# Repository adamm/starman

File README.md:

# Starman Christmas Tree Topper

Disclaimer: This work is a *work-in-progress*.  While this project is still
under active development, version 2.1 was released _December 1st, 2022_.
What you see here is code that is largely incomplete, buggy, crashes,
and could catch fire. The PCB board is largely inefficient, expensive,
broken, and could catch fire.

Version 1 of the star is a POC I created a few years ago which was literally
a 3d-printed star with 24 LEDs hot-glued onto it, driven by a LED PWM
module from Adafruit, 3 PWM channels for audio, running from an Arduino Uno.

Version 2 is a complete redesign for 2022, including a custom PCB, 144
LEDs, 235 components, ESP32-S3 MCU, esp-idf framework, and WiFi/Bluetooth
support.  Audio is driven by 4 PWM channels, featuring a volume control and
a class-D amplifier.

Version 2.1 includes over-the-air firmware updates. I plan on releasing
new themes and songs every Holiday season. 

As of December 2023, there are **7 themes** and **81 arranged songs**.

> [!NOTE]
> I'll be demoing the Starman project, as well demoing its build process at [Calgary Maker Faire, May 4 & 5 2024](https://calgary.makerfaire.com/).
> Come talk to me if you are interested in purchasing a pre-built Starman for Christmas 2024!

You can see v2 in action here: https://www.youtube.com/watch?v=h6fquYPDars

The PCB is created using KiCad:

The sound module connects to the spine of the star through 20mm pin socket
risers.  Finally, a 3d-printed mount secures the display to the christmas
tree's top branch via the risers:

I plan on producing 10 units for friends and family for Christmas 2022.
Right now the costs are too high to mass produce, so perhaps sometime in
2023 I can simplify the design and cut costs for general orders.

## HOW TO PLAY

- Press the button to start the game.
- Start the game with three lives at level 1 (overworld).  If you lose all lives, it's game over.
- There is a 50% chance you will complete each level.  If you do, you move onto next level.  If not, you die and need to retry.
  - Death can occur randomly within the level.
  - Press the button again to start the next level, or retry the same level.
- There is a 40% chance you'll get a star.
  - Stars can occur randomly within the level.
  - Stars do not negate death (ie, falling into a pit).
- There is a 25% chance you'll get a 1-up, resulting in an extra life.
- If you make it to level 4 (castle) and complete it, there is a 25% chance the princess will be there and the game is over.

## Installation

1. Install Starman at the top of your tree, or on your desk, shelf, or wall.
2. Connect the play button remote cable to the play button port.  Hide the play button in your tree, desk, shelf, or wall.
3. Power it on.
4. (Optiona) Connect to your wifi network (see below) to configure the brightness and theme.
5. Press the physical play button, or press Play on the Starman web app

### Wifi Setup

1. Power on the Starman
2. Watch for a "starman_######" access point, and connect to it.
3. Search for your home Wifi, and enter the credentials
  - Starman can only connect to 2.4Ghz/WPA2 endpoints
4. Once connected, wait for your IP address to scroll past the screen
5. Open the IP address in your web browser
  - You can now use this site to play Starman directly, and to access the internal API.

If you ever want to factory reset Starman, follow this procedure:
1. Press and hold *Play* button
2. Press and release *Reset* button
3. Release *Play* button
Starman will forget about its current wifi configuration, theme, and configuration. Follow the Wifi Setup instructions above to set it back up again.

## TODO

- [X] Finalize PCB design
- [X] Play music
- [X] Implement game logic
- [X] Unique light pattern per music song/state
- [X] Flash lights in sequence with music
- [X] GPIO play button
- [X] Show simple text messages
- [X] WiFi onboarding process
- [X] Over-the-air firmware updates
- [X] WiFi play button
- [X] HTTP REST API to push text, play sound
- [X] Brightness control
- [X] Selectable themes
- [ ] Document the REST API
- [ ] Upgrade the speaker from 800mW to 1.5W for more power
- [ ] Debug the RC filter to reduce distortion

## Known Issues

- v2.1 PCB has a label that says it supports 7 to 12 volts power.  *WARNING: only 6-7V is actually supported in v2.1 hardware. __Do not connect more than 7 volts!__*
- Only 2.4Gz WPA2 wifi is supported   (Cannot connect to 5Gz or WPA Enterprise)
- Sound gets distorted at high volume levels.
- It can take a long time after startup to get an IP address and start
  the web service
- Even though wifi and the web service are online and functioning, the
  index.html sometimes takes a long time to load
- Sometimes the device spontaneously resets if wifi connection is not
  stable or strong enough
- Some songs are way too long. (>60s)
- Some songs end way too early (<3s) with a "course completed" event.

## Milestones

2022-09-01
- PCB layout identified and key components selected

2022-09-25
- Components ordered and footprints verified

2022-09-27
- Upgrade from ESP32-S2 to ESP32-S3

2022-09-29
- PCB design delivered for production

2022-10-09
- Complete migration of core game logic from Arduino version (v1) to esp-idf version (v2)

2022-10-29
- Framework for connecting to wifi / performing OTA updates

2022-11-02
- Framework for showing basic text messages, like "Game Over", "Connect to Wifi", "Firmware Update in progress", etc

2022-11-27
- Manufacturing is complete for 10 units for friends and family.

## Key Components

- ESP32-S3-Mini module

- 9x LED1642GW drivers

- 144 OSRAM LY P47 2mm LEDs

- PAM8302A amplifer

- 239 total components (35 unique)

- Translate MIDI to Playtune C array
  - https://github.com/lenshustek/miditones

## Build Dependencies

- See [BUILDING](BUILDING.md) document.

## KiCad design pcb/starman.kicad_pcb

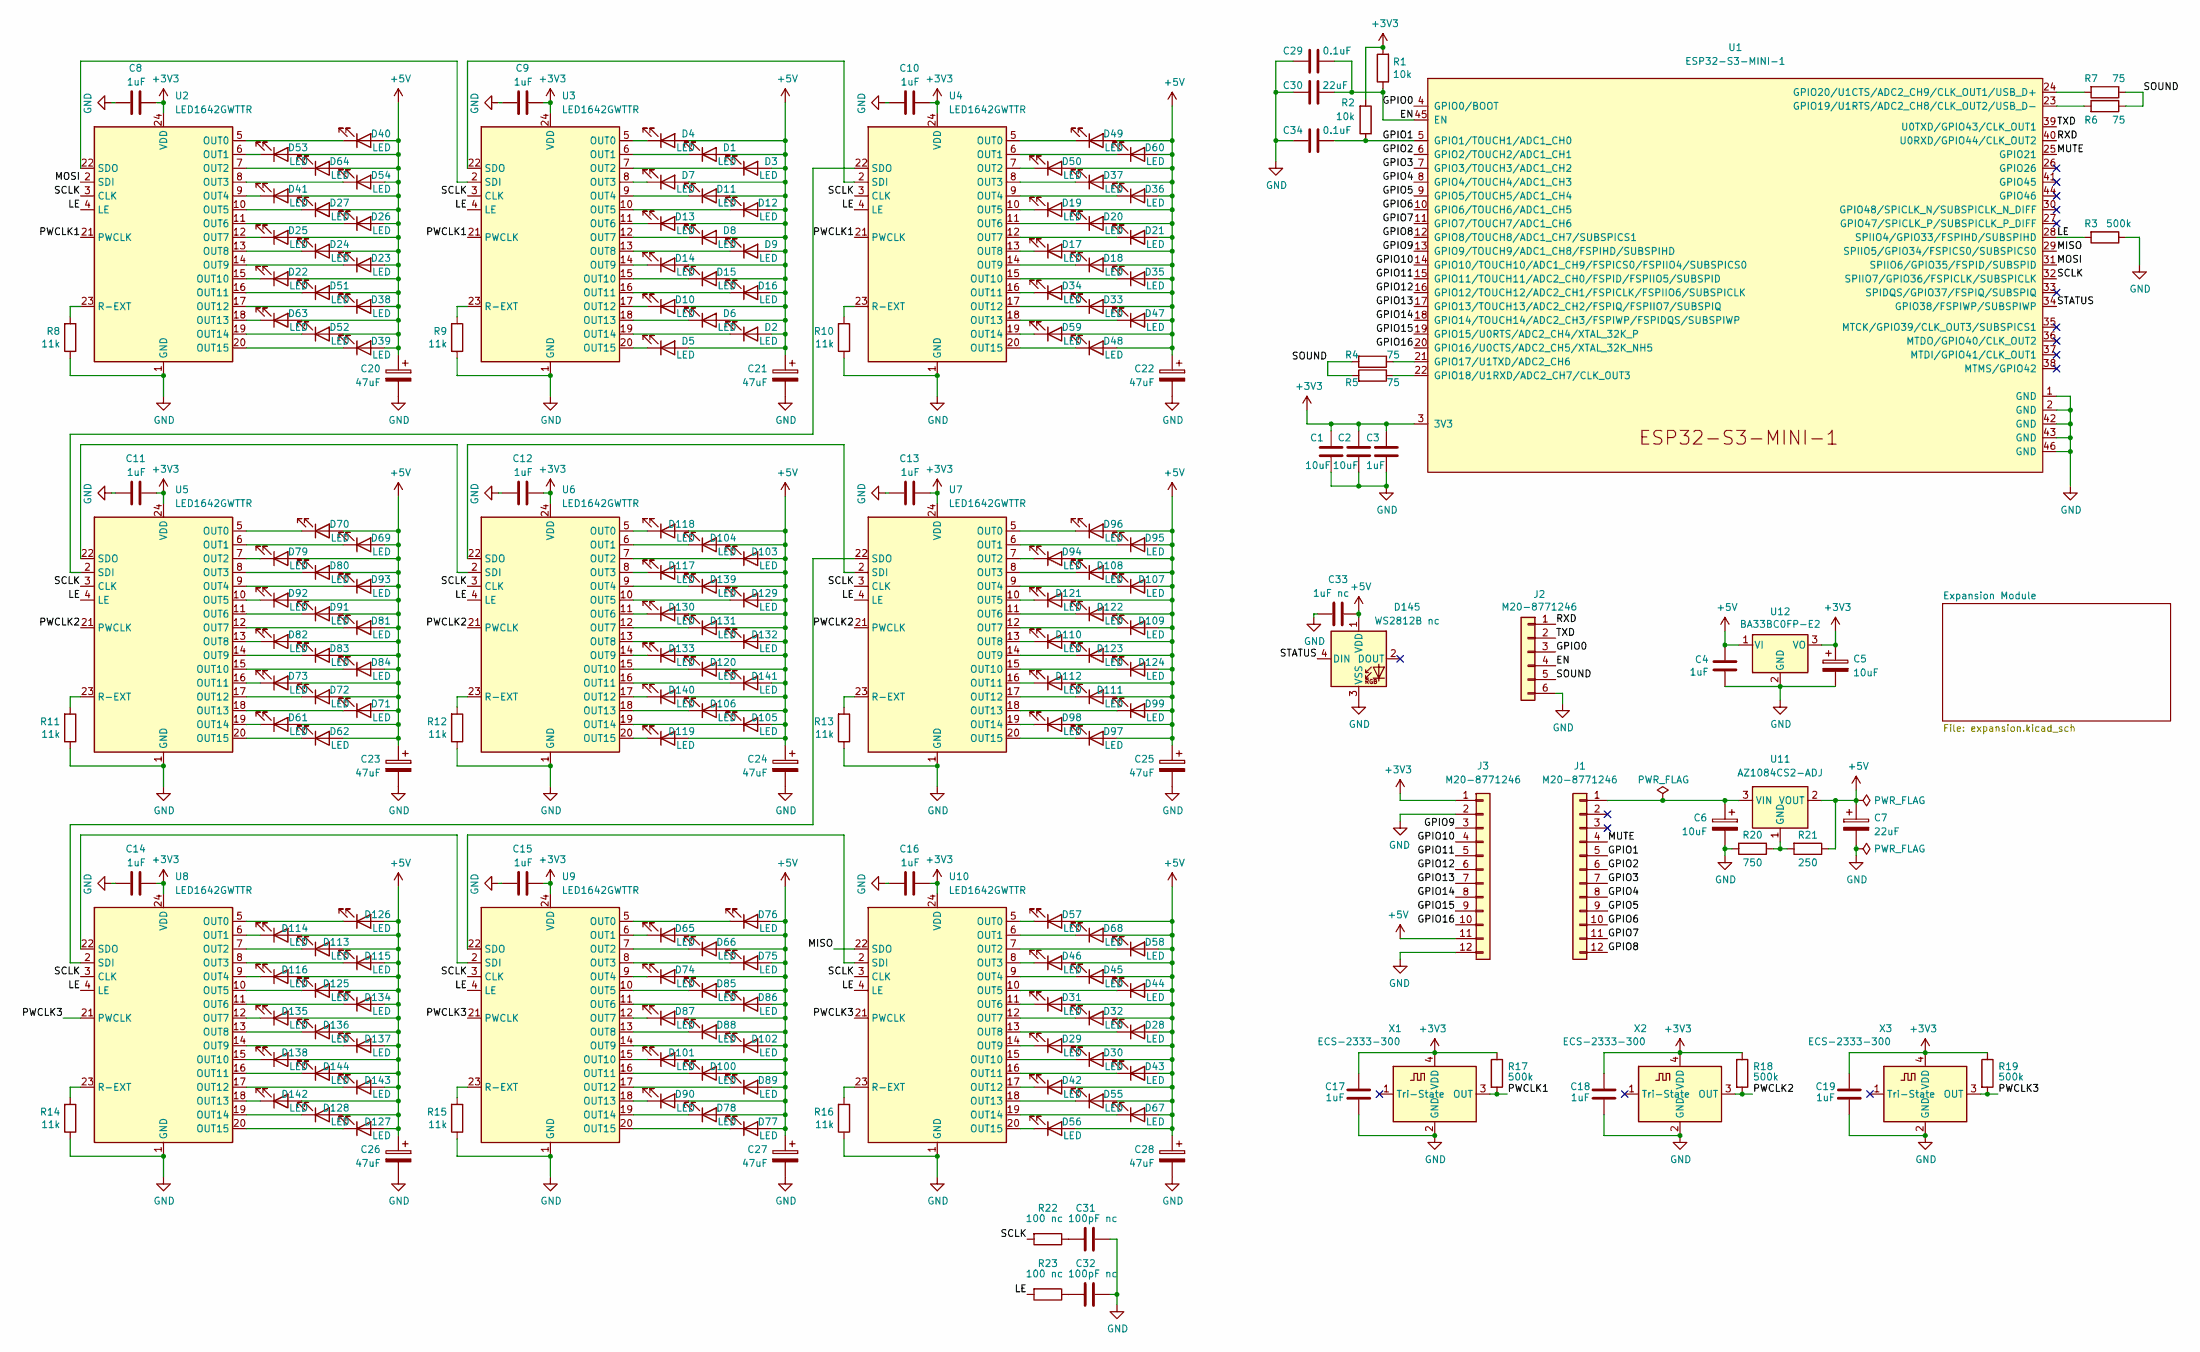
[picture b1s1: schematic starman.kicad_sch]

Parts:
C1, C2: 10uF; C_0805_2012Metric
C3, C4, C8, C9, C10, C11, C12, C13, C14, C15, C16, C17, C18, C19: 1uF; C_0805_2012Metric
C5, C6: 10uF; CP_EIA-3216-10_Kemet-I
C7: 22uF; CP_EIA-3216-10_Kemet-I
C20, C21, C22, C23, C24, C25, C26, C27, C28: 47uF; CP_EIA-3216-10_Kemet-I
C29, C34: 0.1uF; C_0805_2012Metric
C30: 22uF; C_0805_2012Metric
C31, C32: 100pF nc; C_0805_2012Metric
C33: 1uF nc; C_0805_2012Metric
D1, D2, D3, D4, D5, D6, D7, D8, D9, D10, D11, D12, D13, D14, D15, D16, D17, D18, D19, D20, D21, D22, D23, D24, D25, D26, D27, D28, D29, D30, D31, D32, D33, D34, D35, D36, D37, D38, D39, D40, D41, D42, D43, D44, D45, D46, D47, D48, D49, D50, D51, D52, D53, D54, D55, D56, D57, D58, D59, D60, D61, D62, D63, D64, D65, D66, D67, D68, D69, D70, D71, D72, D73, D74, D75, D76, D77, D78, D79, D80, D81, D82, D83, D84, D85, D86, D87, D88, D89, D90, D91, D92, D93, D94, D95, D96, D97, D98, D99, D100, D101, D102, D103, D104, D105, D106, D107, D108, D109, D110, D111, D112, D113, D114, D115, D116, D117, D118, D119, D120, D121, D122, D123, D124, D125, D126, D127, D128, D129, D130, D131, D132, D133, D134, D135, D136, D137, D138, D139, D140, D141, D142, D143, D144: LED; LED_Osram_Lx_P47F_D2mm_ReverseMount
D145: WS2812B nc; LED_WS2812B_PLCC4_5.0x5.0mm_P3.2mm
J1, J3: M20-8771246; PinHeader_1x12_P2.54mm_Vertical_SMD_Pin1Right
J2: M20-8771246; PinHeader_1x06_P2.54mm_Vertical_SMD_Pin1Right
R1, R2: 10k; R_0805_2012Metric
R3, R17, R18, R19: 500k; R_1206_3216Metric
R4, R5, R6, R7: 75; R_0805_2012Metric
R8, R9, R10, R11, R12, R13, R14, R15, R16: 11k; R_0805_2012Metric
R20: 750; R_1206_3216Metric
R21: 250; R_1206_3216Metric
R22, R23: 100 nc; R_0805_2012Metric
U1: ESP32-S3-MINI-1
U2, U3, U4, U5, U6, U7, U8, U9, U10: LED1642GWTTR; TSSOP-24_4.4x7.8mm_P0.65mm
U11: AZ1084CS2-ADJ; TO-263-2
U12: BA33BC0FP-E2; TO-252-2
X1, X2, X3: ECS-2333-300; Oscillator_SMD_ECS_2520MV-xxx-xx-4Pin_2.5x2.0mm

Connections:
+3V3: C1.2, C2.2, C3.2, C5.1, C8.1, C9.1, C10.1, C11.1, C12.1, C13.1, C14.1, C15.1, C16.1, C17.2, C18.2, C19.2, J3.1, R1.2, R2.2, R17.1, R18.1, R19.1, U1.3 (3V3), U2.24 (VDD), U3.24 (VDD), U4.24 (VDD), U5.24 (VDD), U6.24 (VDD), U7.24 (VDD), U8.24 (VDD), U9.24 (VDD), U10.24 (VDD), U12.3 (VO), X1.4 (VDD), X2.4 (VDD), X3.4 (VDD)
+5V: C4.2, C7.1, C20.1, C21.1, C22.1, C23.1, C24.1, C25.1, C26.1, C27.1, C28.1, C33.1, D1.2 (A), D2.2 (A), D3.2 (A), D4.2 (A), D5.2 (A), D6.2 (A), D7.2 (A), D8.2 (A), D9.2 (A), D10.2 (A), D11.2 (A), D12.2 (A), D13.2 (A), D14.2 (A), D15.2 (A), D16.2 (A), D17.2 (A), D18.2 (A), D19.2 (A), D20.2 (A), D21.2 (A), D22.2 (A), D23.2 (A), D24.2 (A), D25.2 (A), D26.2 (A), D27.2 (A), D28.2 (A), D29.2 (A), D30.2 (A), D31.2 (A), D32.2 (A), D33.2 (A), D34.2 (A), D35.2 (A), D36.2 (A), D37.2 (A), D38.2 (A), D39.2 (A), D40.2 (A), D41.2 (A), D42.2 (A), D43.2 (A), D44.2 (A), D45.2 (A), D46.2 (A), D47.2 (A), D48.2 (A), D49.2 (A), D50.2 (A), D51.2 (A), D52.2 (A), D53.2 (A), D54.2 (A), D55.2 (A), D56.2 (A), D57.2 (A), D58.2 (A), D59.2 (A), D60.2 (A), D61.2 (A), D62.2 (A), D63.2 (A), D64.2 (A), D65.2 (A), D66.2 (A), D67.2 (A), D68.2 (A), D69.2 (A), D70.2 (A), D71.2 (A), D72.2 (A), D73.2 (A), D74.2 (A), D75.2 (A), D76.2 (A), D77.2 (A), D78.2 (A), D79.2 (A), D80.2 (A), D81.2 (A), D82.2 (A), D83.2 (A), D84.2 (A), D85.2 (A), D86.2 (A), D87.2 (A), D88.2 (A), D89.2 (A), D90.2 (A), D91.2 (A), D92.2 (A), D93.2 (A), D94.2 (A), D95.2 (A), D96.2 (A), D97.2 (A), D98.2 (A), D99.2 (A), D100.2 (A), D101.2 (A), D102.2 (A), D103.2 (A), D104.2 (A), D105.2 (A), D106.2 (A), D107.2 (A), D108.2 (A), D109.2 (A), D110.2 (A), D111.2 (A), D112.2 (A), D113.2 (A), D114.2 (A), D115.2 (A), D116.2 (A), D117.2 (A), D118.2 (A), D119.2 (A), D120.2 (A), D121.2 (A), D122.2 (A), D123.2 (A), D124.2 (A), D125.2 (A), D126.2 (A), D127.2 (A), D128.2 (A), D129.2 (A), D130.2 (A), D131.2 (A), D132.2 (A), D133.2 (A), D134.2 (A), D135.2 (A), D136.2 (A), D137.2 (A), D138.2 (A), D139.2 (A), D140.2 (A), D141.2 (A), D142.2 (A), D143.2 (A), D144.2 (A), D145.1 (VDD), J3.11, R21.1, U11.2 (VOUT), U12.1 (VI)
/EN: C29.1, C30.1, J2.4, R1.1, U1.45 (EN)
/GPIO0: J2.3, U1.4 (GPIO0/BOOT)
/GPIO1: C34.1, J1.5, R2.1, U1.5 (GPIO1/TOUCH1/ADC1_CH0)
/GPIO2: J1.6, U1.6 (GPIO2/TOUCH2/ADC1_CH1)
/GPIO3: J1.7, U1.7 (GPIO3/TOUCH3/ADC1_CH2)
/GPIO4: J1.8, U1.8 (GPIO4/TOUCH4/ADC1_CH3)
/GPIO5: J1.9, U1.9 (GPIO5/TOUCH5/ADC1_CH4)
/GPIO6: J1.10, U1.10 (GPIO6/TOUCH6/ADC1_CH5)
/GPIO7: J1.11, U1.11 (GPIO7/TOUCH7/ADC1_CH6)
/GPIO8: J1.12, U1.12 (GPIO8/TOUCH8/ADC1_CH7/SUBSPICS1)
/GPIO9: J3.3, U1.13 (GPIO9/TOUCH9/ADC1_CH8/FSPIHD/SUBSPIHD)
/GPIO10: J3.4, U1.14 (GPIO10/TOUCH10/ADC1_CH9/FSPICS0/FSPIIO4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)
/GPIO11: J3.5, U1.15 (GPIO11/TOUCH11/ADC2_CH0/FSPID/FSPIIO5/S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)
/GPIO12: J3.6, U1.16 (GPIO12/TOUCH12/ADC2_CH1/FSPICLK/FSPIIO6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)
/GPIO13: J3.7, U1.17 (GPIO13/TOUCH13/ADC2_CH2/FSPIQ/FSPIIO7/S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)
/GPIO14: J3.8, U1.18 (GPIO14/TOUCH14/ADC2_CH3/FSPIWP/FSPIDQS/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)
/GPIO15: J3.9, U1.19 (GPIO15/U0RTS/ADC2_CH4/XTAL_32K_P)
/GPIO16: J3.10, U1.20 (GPIO16/U0CTS/ADC2_CH5/XTAL_32K_NH5)
/LE: R3.2, R23.2, U1.28 (SPIIO4/GPIO33/FSPIHD/SUBSPIHD), U2.4 (LE), U3.4 (LE), U4.4 (LE), U5.4 (LE), U6.4 (LE), U7.4 (LE), U8.4 (LE), U9.4 (LE), U10.4 (LE)
/MISO: U1.29 (SPIIO5/GPIO34/FSPICS0/SUBSPICS0), U10.22 (SDO)
/MOSI: U1.31 (SPIIO6/GPIO35/FSPID/SUBSPID), U2.2 (SDI)
/MUTE: J1.4, U1.25 (GPIO21)
/PWCLK1: R17.2, U2.21 (PWCLK), U3.21 (PWCLK), U4.21 (PWCLK), X1.3 (OUT)
/PWCLK2: R18.2, U5.21 (PWCLK), U6.21 (PWCLK), U7.21 (PWCLK), X2.3 (OUT)
/PWCLK3: R19.2, U8.21 (PWCLK), U9.21 (PWCLK), U10.21 (PWCLK), X3.3 (OUT)
/RXD: J2.1, U1.40 (U0RXD/GPIO44/CLK_OUT2)
/SCLK: R22.2, U1.32 (SPIIO7/GPIO36/FSPICLK/SUBSPICLK), U2.3 (CLK), U3.3 (CLK), U4.3 (CLK), U5.3 (CLK), U6.3 (CLK), U7.3 (CLK), U8.3 (CLK), U9.3 (CLK), U10.3 (CLK)
/SOUND: J2.5, R4.2, R5.2, R6.1, R7.1
/STATUS: D145.4 (DIN), U1.34 (GPIO38/FSPIWP/SUBSPIWP)
/TXD: J2.2, U1.39 (U0TXD/GPIO43/CLK_OUT1)
GND: C1.1, C2.1, C3.1, C4.1, C5.2, C6.2, C7.2, C8.2, C9.2, C10.2, C11.2, C12.2, C13.2, C14.2, C15.2, C16.2, C17.1, C18.1, C19.1, C20.2, C21.2, C22.2, C23.2, C24.2, C25.2, C26.2, C27.2, C28.2, C29.2, C30.2, C31.1, C32.1, C33.2, C34.2, D145.3 (VSS), J2.6, J3.2, J3.12, R3.1, R8.1, R9.1, R10.1, R11.1, R12.1, R13.1, R14.1, R15.1, R16.1, R20.2, U1.1 (GND), U1.2 (GND), U1.42 (GND), U1.43 (GND), U1.46 (GND), U2.1 (GND), U3.1 (GND), U4.1 (GND), U5.1 (GND), U6.1 (GND), U7.1 (GND), U8.1 (GND), U9.1 (GND), U10.1 (GND), U12.2 (GND), X1.2 (GND), X2.2 (GND), X3.2 (GND)
unnamed: C6.1, J1.1, U11.3 (VIN)
unnamed: C31.2, R22.1
unnamed: C32.2, R23.1
unnamed: D1.1 (K), U3.6 (OUT1)
unnamed: D2.1 (K), U3.19 (OUT14)
unnamed: D3.1 (K), U3.7 (OUT2)
unnamed: D4.1 (K), U3.5 (OUT0)
unnamed: D5.1 (K), U3.20 (OUT15)
unnamed: D6.1 (K), U3.18 (OUT13)
unnamed: D7.1 (K), U3.8 (OUT3)
unnamed: D8.1 (K), U3.12 (OUT7)
unnamed: D9.1 (K), U3.13 (OUT8)
unnamed: D10.1 (K), U3.17 (OUT12)
unnamed: D11.1 (K), U3.9 (OUT4)
unnamed: D12.1 (K), U3.10 (OUT5)
unnamed: D13.1 (K), U3.11 (OUT6)
unnamed: D14.1 (K), U3.14 (OUT9)
unnamed: D15.1 (K), U3.15 (OUT10)
unnamed: D16.1 (K), U3.16 (OUT11)
unnamed: D17.1 (K), U4.13 (OUT8)
unnamed: D18.1 (K), U4.14 (OUT9)
unnamed: D19.1 (K), U4.10 (OUT5)
unnamed: D20.1 (K), U4.11 (OUT6)
unnamed: D21.1 (K), U4.12 (OUT7)
unnamed: D22.1 (K), U2.15 (OUT10)
unnamed: D23.1 (K), U2.14 (OUT9)
unnamed: D24.1 (K), U2.13 (OUT8)
unnamed: D25.1 (K), U2.12 (OUT7)
unnamed: D26.1 (K), U2.11 (OUT6)
unnamed: D27.1 (K), U2.10 (OUT5)
unnamed: D28.1 (K), U10.13 (OUT8)
unnamed: D29.1 (K), U10.14 (OUT9)
unnamed: D30.1 (K), U10.15 (OUT10)
unnamed: D31.1 (K), U10.11 (OUT6)
unnamed: D32.1 (K), U10.12 (OUT7)
unnamed: D33.1 (K), U4.17 (OUT12)
unnamed: D34.1 (K), U4.16 (OUT11)
unnamed: D35.1 (K), U4.15 (OUT10)
unnamed: D36.1 (K), U4.9 (OUT4)
unnamed: D37.1 (K), U4.8 (OUT3)
unnamed: D38.1 (K), U2.17 (OUT12)
unnamed: D39.1 (K), U2.20 (OUT15)
unnamed: D40.1 (K), U2.5 (OUT0)
unnamed: D41.1 (K), U2.9 (OUT4)
unnamed: D42.1 (K), U10.17 (OUT12)
unnamed: D43.1 (K), U10.16 (OUT11)
unnamed: D44.1 (K), U10.10 (OUT5)
unnamed: D45.1 (K), U10.9 (OUT4)
unnamed: D46.1 (K), U10.8 (OUT3)
unnamed: D47.1 (K), U4.18 (OUT13)
unnamed: D48.1 (K), U4.20 (OUT15)
unnamed: D49.1 (K), U4.5 (OUT0)
unnamed: D50.1 (K), U4.7 (OUT2)
unnamed: D51.1 (K), U2.16 (OUT11)
unnamed: D52.1 (K), U2.19 (OUT14)
unnamed: D53.1 (K), U2.6 (OUT1)
unnamed: D54.1 (K), U2.8 (OUT3)
unnamed: D55.1 (K), U10.18 (OUT13)
unnamed: D56.1 (K), U10.20 (OUT15)
unnamed: D57.1 (K), U10.5 (OUT0)
unnamed: D58.1 (K), U10.7 (OUT2)
unnamed: D59.1 (K), U4.19 (OUT14)
unnamed: D60.1 (K), U4.6 (OUT1)
unnamed: D61.1 (K), U5.19 (OUT14)
unnamed: D62.1 (K), U5.20 (OUT15)
unnamed: D63.1 (K), U2.18 (OUT13)
unnamed: D64.1 (K), U2.7 (OUT2)
unnamed: D65.1 (K), U9.6 (OUT1)
unnamed: D66.1 (K), U9.7 (OUT2)
unnamed: D67.1 (K), U10.19 (OUT14)
unnamed: D68.1 (K), U10.6 (OUT1)
unnamed: D69.1 (K), U5.6 (OUT1)
unnamed: D70.1 (K), U5.5 (OUT0)
unnamed: D71.1 (K), U5.18 (OUT13)
unnamed: D72.1 (K), U5.17 (OUT12)
unnamed: D73.1 (K), U5.16 (OUT11)
unnamed: D74.1 (K), U9.9 (OUT4)
unnamed: D75.1 (K), U9.8 (OUT3)
unnamed: D76.1 (K), U9.5 (OUT0)
unnamed: D77.1 (K), U9.20 (OUT15)
unnamed: D78.1 (K), U9.19 (OUT14)
unnamed: D79.1 (K), U5.7 (OUT2)
unnamed: D80.1 (K), U5.8 (OUT3)
unnamed: D81.1 (K), U5.12 (OUT7)
unnamed: D82.1 (K), U5.13 (OUT8)
unnamed: D83.1 (K), U5.14 (OUT9)
unnamed: D84.1 (K), U5.15 (OUT10)
unnamed: D85.1 (K), U9.10 (OUT5)
unnamed: D86.1 (K), U9.11 (OUT6)
unnamed: D87.1 (K), U9.12 (OUT7)
unnamed: D88.1 (K), U9.13 (OUT8)
unnamed: D89.1 (K), U9.17 (OUT12)
unnamed: D90.1 (K), U9.18 (OUT13)
unnamed: D91.1 (K), U5.11 (OUT6)
unnamed: D92.1 (K), U5.10 (OUT5)
unnamed: D93.1 (K), U5.9 (OUT4)
unnamed: D94.1 (K), U7.7 (OUT2)
unnamed: D95.1 (K), U7.6 (OUT1)
unnamed: D96.1 (K), U7.5 (OUT0)
unnamed: D97.1 (K), U7.20 (OUT15)
unnamed: D98.1 (K), U7.19 (OUT14)
unnamed: D99.1 (K), U7.18 (OUT13)
unnamed: D100.1 (K), U9.16 (OUT11)
unnamed: D101.1 (K), U9.15 (OUT10)
unnamed: D102.1 (K), U9.14 (OUT9)
unnamed: D103.1 (K), U6.7 (OUT2)
unnamed: D104.1 (K), U6.6 (OUT1)
unnamed: D105.1 (K), U6.19 (OUT14)
unnamed: D106.1 (K), U6.18 (OUT13)
unnamed: D107.1 (K), U7.9 (OUT4)
unnamed: D108.1 (K), U7.8 (OUT3)
unnamed: D109.1 (K), U7.12 (OUT7)
unnamed: D110.1 (K), U7.13 (OUT8)
unnamed: D111.1 (K), U7.17 (OUT12)
unnamed: D112.1 (K), U7.16 (OUT11)
unnamed: D113.1 (K), U8.7 (OUT2)
unnamed: D114.1 (K), U8.6 (OUT1)
unnamed: D115.1 (K), U8.8 (OUT3)
unnamed: D116.1 (K), U8.9 (OUT4)
unnamed: D117.1 (K), U6.8 (OUT3)
unnamed: D118.1 (K), U6.5 (OUT0)
unnamed: D119.1 (K), U6.20 (OUT15)
unnamed: D120.1 (K), U6.15 (OUT10)
unnamed: D121.1 (K), U7.10 (OUT5)
unnamed: D122.1 (K), U7.11 (OUT6)
unnamed: D123.1 (K), U7.14 (OUT9)
unnamed: D124.1 (K), U7.15 (OUT10)
unnamed: D125.1 (K), U8.10 (OUT5)
unnamed: D126.1 (K), U8.5 (OUT0)
unnamed: D127.1 (K), U8.20 (OUT15)
unnamed: D128.1 (K), U8.19 (OUT14)
unnamed: D129.1 (K), U6.10 (OUT5)
unnamed: D130.1 (K), U6.11 (OUT6)
unnamed: D131.1 (K), U6.12 (OUT7)
unnamed: D132.1 (K), U6.13 (OUT8)
unnamed: D133.1 (K), U6.14 (OUT9)
unnamed: D134.1 (K), U8.11 (OUT6)
unnamed: D135.1 (K), U8.12 (OUT7)
unnamed: D136.1 (K), U8.13 (OUT8)
unnamed: D137.1 (K), U8.14 (OUT9)
unnamed: D138.1 (K), U8.15 (OUT10)
unnamed: D139.1 (K), U6.9 (OUT4)
unnamed: D140.1 (K), U6.17 (OUT12)
unnamed: D141.1 (K), U6.16 (OUT11)
unnamed: D142.1 (K), U8.18 (OUT13)
unnamed: D143.1 (K), U8.17 (OUT12)
unnamed: D144.1 (K), U8.16 (OUT11)
unnamed: R4.1, U1.21 (GPIO17/U1TXD/ADC2_CH6)
unnamed: R5.1, U1.22 (GPIO18/U1RXD/ADC2_CH7/CLK_OUT3)
unnamed: R6.2, U1.23 (GPIO19/U1RTS/ADC2_CH8/CLK_OUT2/USB_D-)
unnamed: R7.2, U1.24 (GPIO20/U1CTS/ADC2_CH9/CLK_OUT1/USB_D+)
unnamed: R8.2, U2.23 (R-EXT)
unnamed: R9.2, U3.23 (R-EXT)
unnamed: R10.2, U4.23 (R-EXT)
unnamed: R11.2, U5.23 (R-EXT)
unnamed: R12.2, U6.23 (R-EXT)
unnamed: R13.2, U7.23 (R-EXT)
unnamed: R14.2, U8.23 (R-EXT)
unnamed: R15.2, U9.23 (R-EXT)
unnamed: R16.2, U10.23 (R-EXT)
unnamed: R20.1, R21.2, U11.1 (GND)
unnamed: U2.22 (SDO), U3.2 (SDI)
unnamed: U3.22 (SDO), U4.2 (SDI)
unnamed: U4.22 (SDO), U5.2 (SDI)
unnamed: U5.22 (SDO), U6.2 (SDI)
unnamed: U6.22 (SDO), U7.2 (SDI)
unnamed: U7.22 (SDO), U8.2 (SDI)
unnamed: U8.22 (SDO), U9.2 (SDI)
unnamed: U9.22 (SDO), U10.2 (SDI)

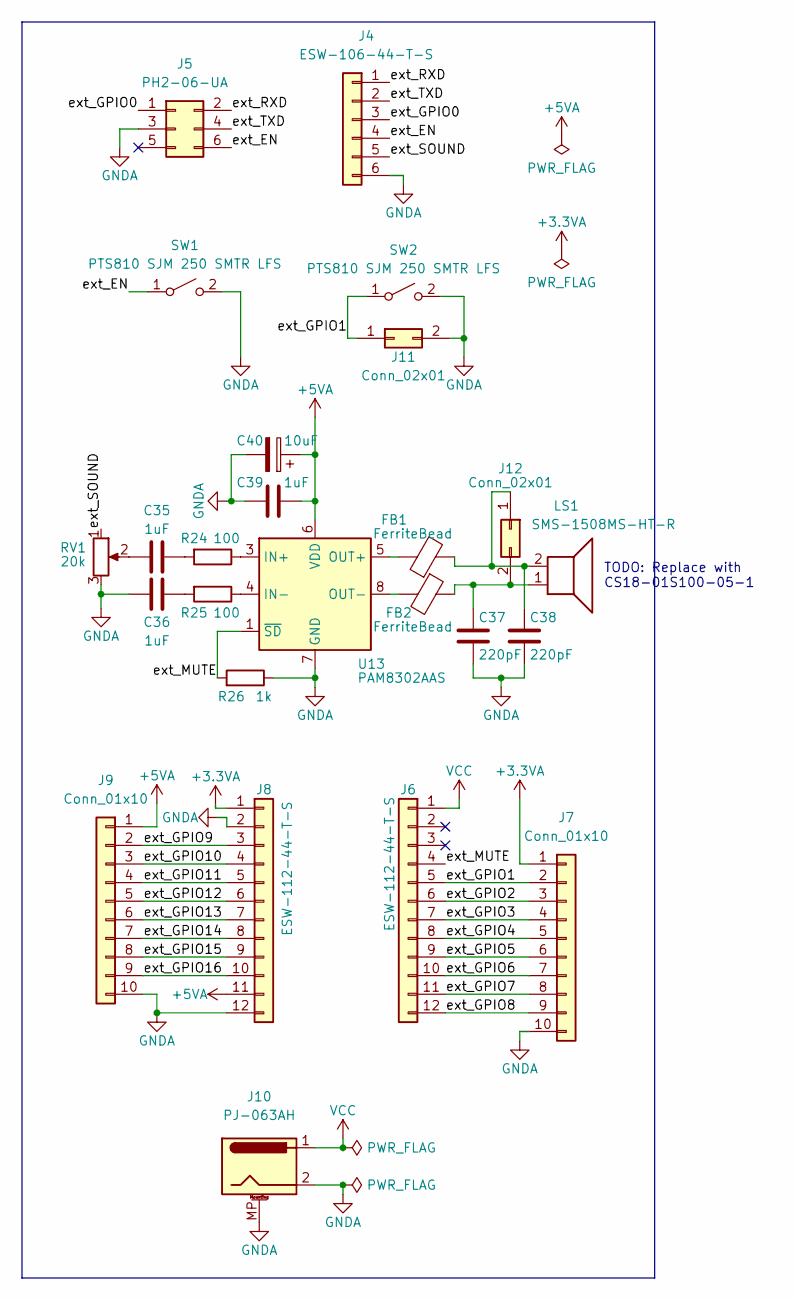
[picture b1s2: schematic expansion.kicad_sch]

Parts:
C35, C36, C39: 1uF; C_0805_2012Metric
C37, C38: 220pF; C_0805_2012Metric
C40: 10uF; CP_EIA-3216-10_Kemet-I
FB1, FB2: FerriteBead; C_0805_2012Metric
J4: ESW-106-44-T-S; PinSocket_1x06_P2.54mm_Vertical
J5: PH2-06-UA; PinHeader_2x03_P2.54mm_Vertical
J6, J8: ESW-112-44-T-S; PinSocket_1x12_P2.54mm_Vertical
J7, J9: Conn_01x10; PinHeader_1x10_P2.54mm_Vertical
J10: PJ-063AH; BarrelJack_CUI_PJ-063AH_Horizontal
J11, J12: Conn_02x01; PinHeader_1x02_P2.54mm_Vertical
LS1: SMS-1508MS-HT-R; SPKR_SMS-1508MS-HT-R
R24, R25: 100; R_0805_2012Metric
R26: 1k; R_0805_2012Metric
RV1: 20k; Potentiometer_Bourns_3339P_Vertical
SW1, SW2: PTS810 SJM 250 SMTR LFS; SW_SPST_PTS810
U13: PAM8302AAS; SOP-8_3.9x4.9mm_P1.27mm

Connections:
+3.3VA: J7.1, J8.1
+5VA: C39.1, C40.1, J8.11, J9.1, U13.6 (VDD)
/Expansion Module/ext_EN: J4.4, J5.6, SW1.1 (A)
/Expansion Module/ext_GPIO0: J4.3, J5.1
/Expansion Module/ext_GPIO1: J6.5, J7.2, J11.1, SW2.1 (A)
/Expansion Module/ext_GPIO2: J6.6, J7.3
/Expansion Module/ext_GPIO3: J6.7, J7.4
/Expansion Module/ext_GPIO4: J6.8, J7.5
/Expansion Module/ext_GPIO5: J6.9, J7.6
/Expansion Module/ext_GPIO6: J6.10, J7.7
/Expansion Module/ext_GPIO7: J6.11, J7.8
/Expansion Module/ext_GPIO8: J6.12, J7.9
/Expansion Module/ext_GPIO9: J8.3, J9.2
/Expansion Module/ext_GPIO10: J8.4, J9.3
/Expansion Module/ext_GPIO11: J8.5, J9.4
/Expansion Module/ext_GPIO12: J8.6, J9.5
/Expansion Module/ext_GPIO13: J8.7, J9.6
/Expansion Module/ext_GPIO14: J8.8, J9.7
/Expansion Module/ext_GPIO15: J8.9, J9.8
/Expansion Module/ext_GPIO16: J8.10, J9.9
/Expansion Module/ext_MUTE: J6.4, R26.2, U13.1 (~SD)
/Expansion Module/ext_RXD: J4.1, J5.2
/Expansion Module/ext_SOUND: J4.5, RV1.1
/Expansion Module/ext_TXD: J4.2, J5.4
GNDA: C36.2, C37.2, C38.2, C39.2, C40.2, J4.6, J5.3, J7.10, J8.2, J8.12, J9.10, J10.2, J10.MP (MountPin), J11.2, R26.1, RV1.3, SW1.2 (B), SW2.2 (B), U13.7 (GND)
unnamed: C35.1, R24.2
unnamed: C35.2, RV1.2
unnamed: C36.1, R25.2
unnamed: C37.1, FB2.1, J12.2, LS1.1
unnamed: C38.1, FB1.2, J12.1, LS1.2
unnamed: FB1.1, U13.5 (OUT+)
unnamed: FB2.2, U13.8 (OUT-)
unnamed: R24.1, U13.3 (IN+)
unnamed: R25.1, U13.4 (IN-)
VCC: J6.1, J10.1

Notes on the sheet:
TODO: Replace with CS18-01S100-05-1

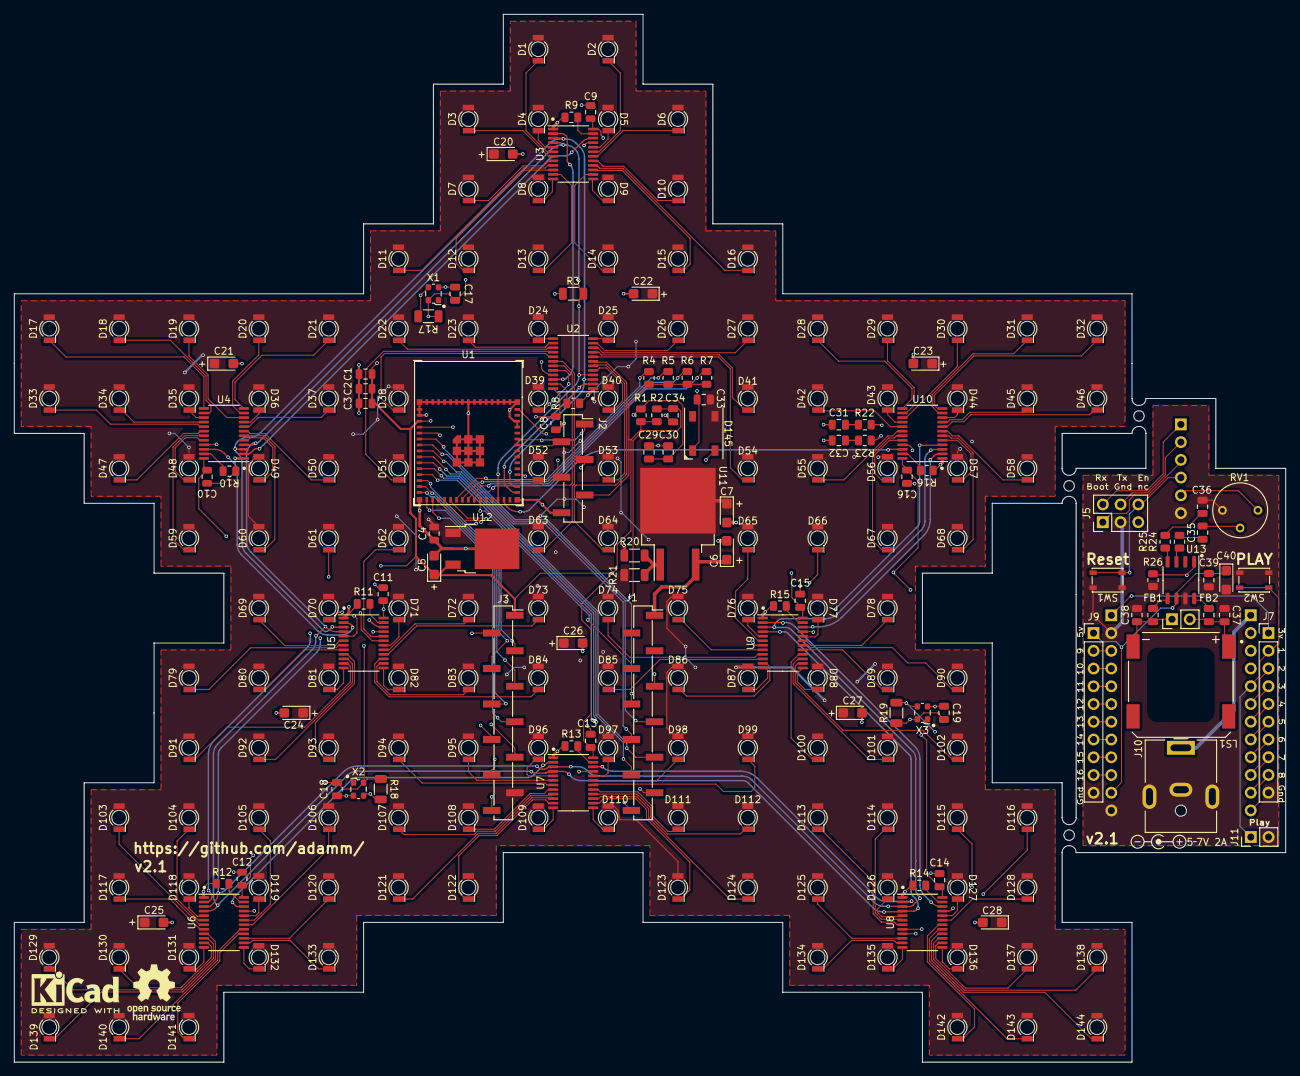
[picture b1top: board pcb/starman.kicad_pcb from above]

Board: 4 copper layers, 182.0 x 150.0 mm, 247 parts (0 on the bottom side), 237 nets.

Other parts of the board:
LOGO1: KiCad-Logo2_5mm_SilkScreen
LOGO2: OSHW-Logo_7.5x8mm_SilkScreen

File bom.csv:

"Refs","Value","Footprint","Qty","DNP"
"C1, C2, C5, C6, C40","10uF","Capacitor_SMD:C_0805_2012Metric,Capacitor_Tantalum_SMD:CP_EIA-3216-10_Kemet-I","5",""
"C3, C4, C8-C19, C35, C36, C39","1uF","Capacitor_SMD:C_0805_2012Metric","17",""
"C7, C30","22uF","Capacitor_SMD:C_0805_2012Metric,Capacitor_Tantalum_SMD:CP_EIA-3216-10_Kemet-I","2",""
"C20-C28","47uF","Capacitor_Tantalum_SMD:CP_EIA-3216-10_Kemet-I","9",""
"C29, C34","0.1uF","Capacitor_SMD:C_0805_2012Metric","2",""
"C33","1uF nc","Capacitor_SMD:C_0805_2012Metric","1",""
"C37, C38","220pF","Capacitor_SMD:C_0805_2012Metric","2",""
"D1-D144","LED","starman:LED_Osram_Lx_P47F_D2mm_ReverseMount","144",""
"D145","WS2812B nc","LED_SMD:LED_WS2812B_PLCC4_5.0x5.0mm_P3.2mm","1",""
"FB1, FB2","FerriteBead","Capacitor_SMD:C_0805_2012Metric","2",""
"J1-J3","M20-8771246","Connector_PinHeader_2.54mm:PinHeader_1x06_P2.54mm_Vertical_SMD_Pin1Right,Connector_PinHeader_2.54mm:PinHeader_1x12_P2.54mm_Vertical_SMD_Pin1Right","3",""
"J4","ESW-106-44-T-S","Connector_PinSocket_2.54mm:PinSocket_1x06_P2.54mm_Vertical","1",""
"J5","PH2-06-UA","Connector_PinHeader_2.54mm:PinHeader_2x03_P2.54mm_Vertical","1",""
"J6, J8","ESW-112-44-T-S","Connector_PinSocket_2.54mm:PinSocket_1x12_P2.54mm_Vertical","2",""
"J7, J9","Conn_01x10","Connector_PinHeader_2.54mm:PinHeader_1x10_P2.54mm_Vertical","2",""
"J10","PJ-063AH","Connector_BarrelJack:BarrelJack_CUI_PJ-063AH_Horizontal","1",""
"J11, J12","Conn_02x01","Connector_PinHeader_2.54mm:PinHeader_1x02_P2.54mm_Vertical","2",""
"LS1","SMS-1508MS-HT-R","starman:SPKR_SMS-1508MS-HT-R","1",""
"R1, R2","10k","Resistor_SMD:R_0805_2012Metric","2",""
"R3, R17-R19","500k","Resistor_SMD:R_1206_3216Metric","4",""
"R4-R7","75","Resistor_SMD:R_0805_2012Metric","4",""
"R8-R16","11k","Resistor_SMD:R_0805_2012Metric","9",""
"R20","750","Resistor_SMD:R_1206_3216Metric","1",""
"R21","250","Resistor_SMD:R_1206_3216Metric","1",""
"R24, R25","100","Resistor_SMD:R_0805_2012Metric","2",""
"R26","1k","Resistor_SMD:R_0805_2012Metric","1",""
"RV1","20k","Potentiometer_THT:Potentiometer_Bourns_3339P_Vertical","1",""
"SW1, SW2","PTS810 SJM 250 SMTR LFS","Button_Switch_SMD:SW_SPST_PTS810","2",""
"U1","ESP32-S3-MINI-1","Espressif:ESP32-S3-MINI-1","1",""
"U2-U10","LED1642GWTTR","Package_SO:TSSOP-24_4.4x7.8mm_P0.65mm","9",""
"U11","AZ1084CS2-ADJ","Package_TO_SOT_SMD:TO-263-2","1",""
"U12","BA33BC0FP-E2","Package_TO_SOT_SMD:TO-252-2","1",""
"U13","PAM8302AAS","Package_SO:SOP-8_3.9x4.9mm_P1.27mm","1",""
"X1-X3","ECS-2333-300","Oscillator:Oscillator_SMD_ECS_2520MV-xxx-xx-4Pin_2.5x2.0mm","3",""
